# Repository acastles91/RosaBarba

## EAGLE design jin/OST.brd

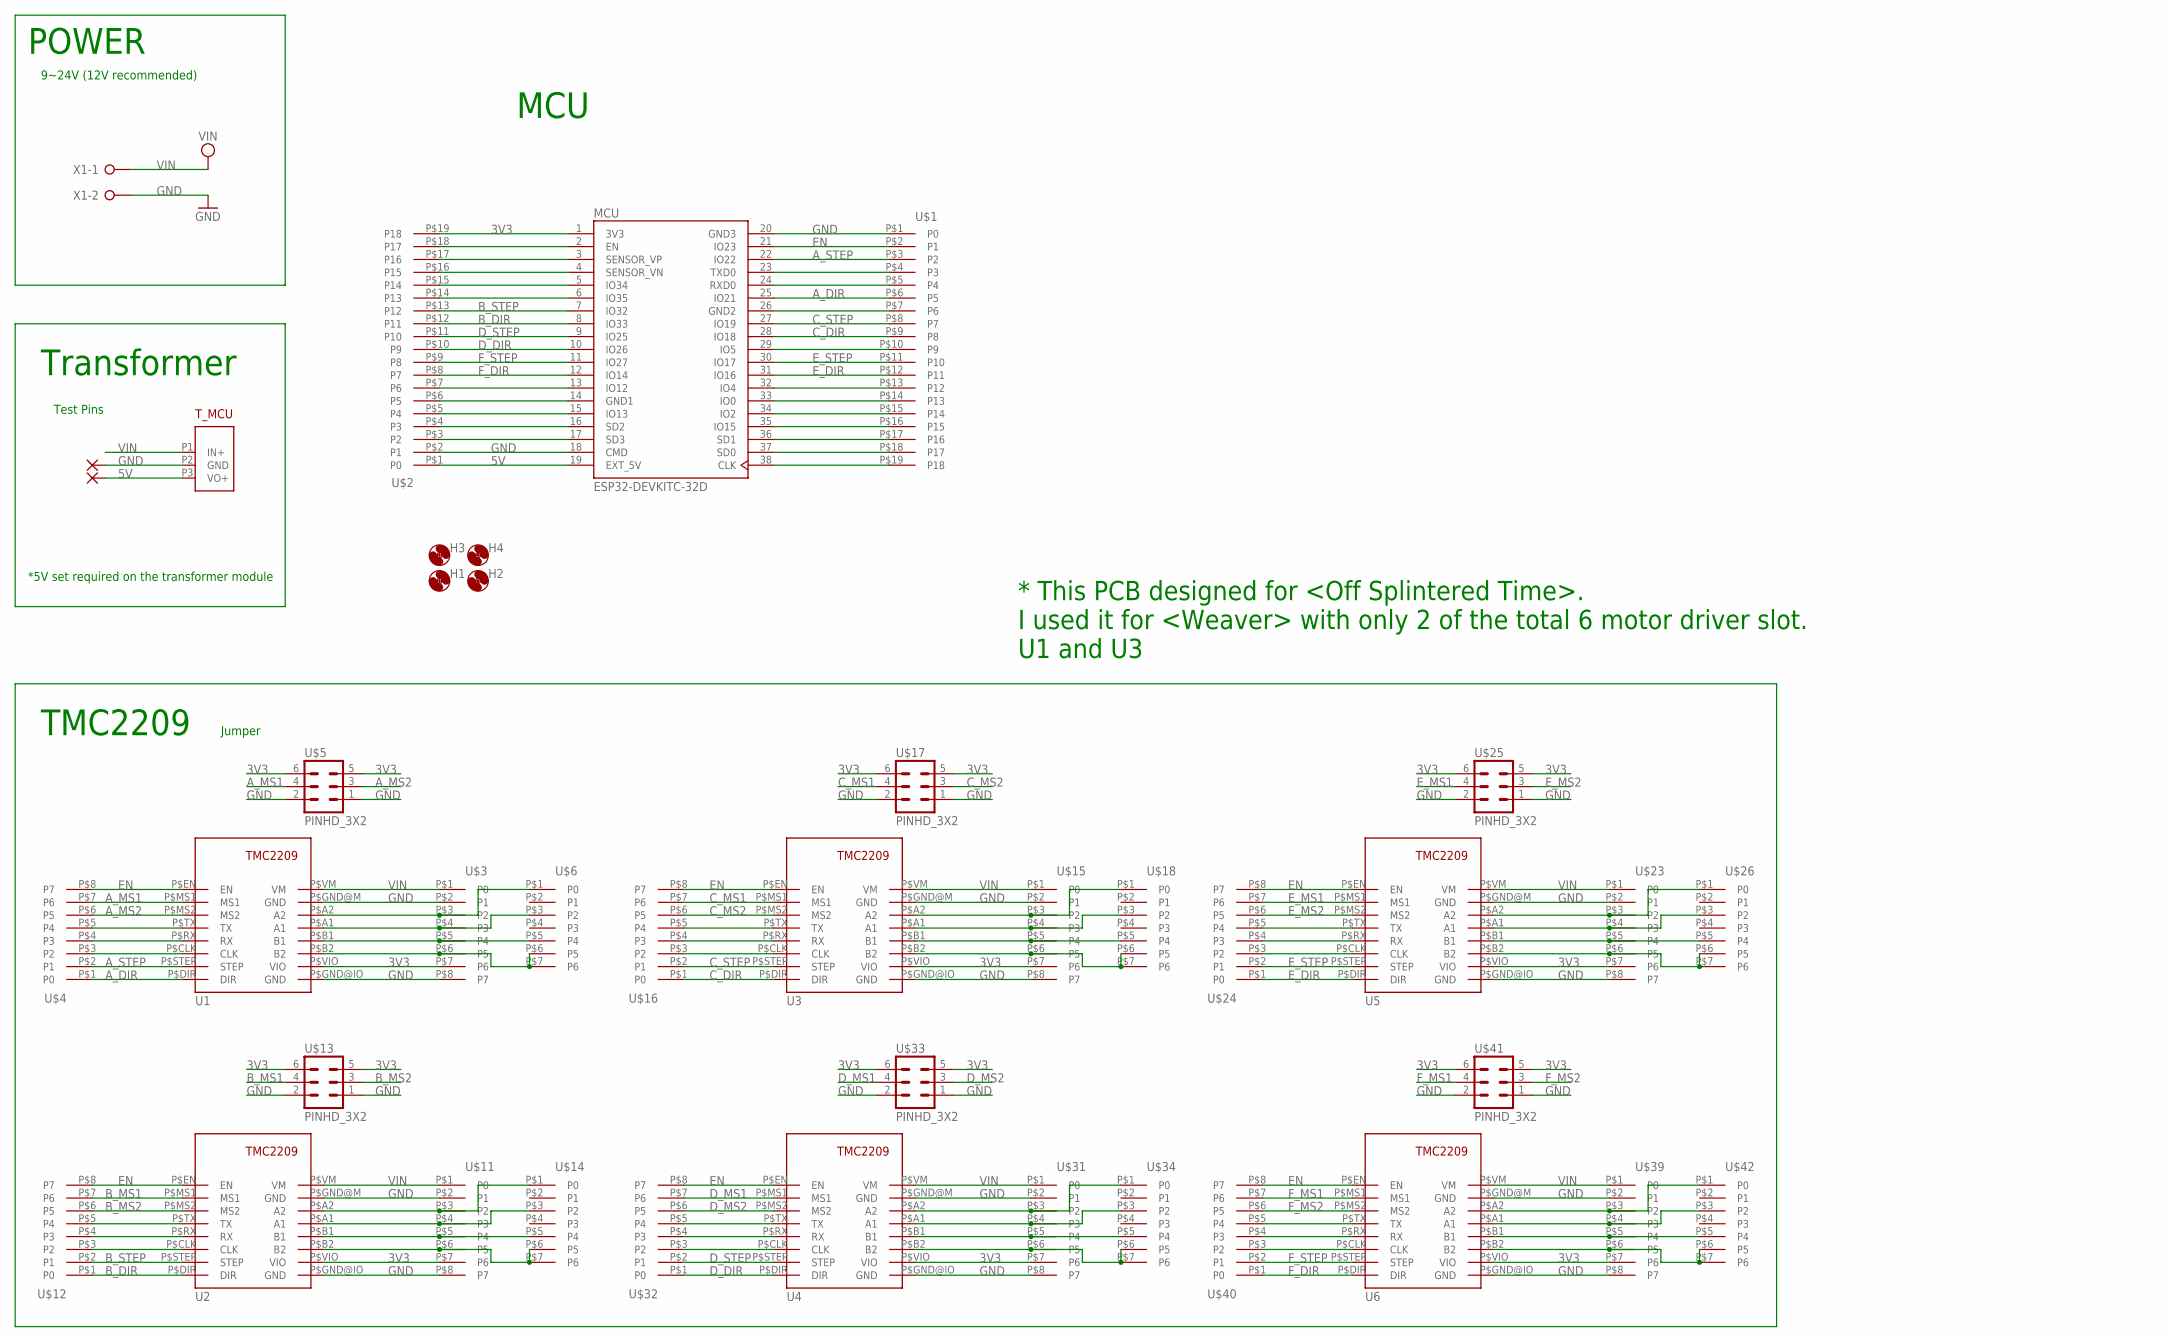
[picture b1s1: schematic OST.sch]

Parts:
H1, H2, H3, H4: MOUNT-HOLE3.2; 3,2
MCU: ESP32-DEVKITC-32D; MODULE_ESP32-DEVKITC-32D
PAD16, PAD17: 2,15/1,0
T_MCU: VOL_ADJ; FREEVOL
U1, U2, U3, U4, U5, U6: TMC2209_V3.1; TMC2209
U$1, U$2: PINHD_1X19; 19
U$3, U$4, U$11, U$12, U$15, U$16, U$23, U$24, U$31, U$32, U$39, U$40: PINHD_1X8; 8
U$5, U$13, U$17, U$25, U$33, U$41: PINHD_3X2; MA03-2
U$6, U$14, U$18, U$26, U$34, U$42: PINHD_1X7; 7
X1: W237-02P; W237-132

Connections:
3V3: MCU.1 (3V3), U1.P$VIO (VIO), U2.P$VIO (VIO), U3.P$VIO (VIO), U4.P$VIO (VIO), U5.P$VIO (VIO), U6.P$VIO (VIO), U$2.P$19 (P18), U$3.P$7 (P6), U$5.5, U$5.6, U$11.P$7 (P6), U$13.5, U$13.6, U$15.P$7 (P6), U$17.5, U$17.6, U$23.P$7 (P6), U$25.5, U$25.6, U$31.P$7 (P6), U$33.5, U$33.6, U$39.P$7 (P6), U$41.5, U$41.6
5V: MCU.19 (EXT_5V), PAD17.1, T_MCU.P3 (VO+), U$2.P$1 (P0)
A1: U1.P$A1 (A1), U$3.P$4 (P3), U$6.P$3 (P2)
A2: U1.P$A2 (A2), U$3.P$3 (P2), U$6.P$1 (P0)
A5: U2.P$A2 (A2), U$11.P$3 (P2), U$14.P$1 (P0)
A6: U2.P$A1 (A1), U$11.P$4 (P3), U$14.P$3 (P2)
A7: U3.P$A2 (A2), U$15.P$3 (P2), U$18.P$1 (P0)
A8: U3.P$A1 (A1), U$15.P$4 (P3), U$18.P$3 (P2)
A11: U5.P$A2 (A2), U$23.P$3 (P2), U$26.P$1 (P0)
A12: U5.P$A1 (A1), U$23.P$4 (P3), U$26.P$3 (P2)
A15: U4.P$A2 (A2), U$31.P$3 (P2), U$34.P$1 (P0)
A16: U4.P$A1 (A1), U$31.P$4 (P3), U$34.P$3 (P2)
A19: U6.P$A2 (A2), U$39.P$3 (P2), U$42.P$1 (P0)
A20: U6.P$A1 (A1), U$39.P$4 (P3), U$42.P$3 (P2)
A_DIR: MCU.25 (IO21), U1.P$DIR (DIR), U$1.P$6 (P5), U$4.P$1 (P0)
A_MS1: U1.P$MS1 (MS1), U$4.P$7 (P6), U$5.4
A_MS2: U1.P$MS2 (MS2), U$4.P$6 (P5), U$5.3
A_STEP: MCU.22 (IO22), U1.P$STEP (STEP), U$1.P$3 (P2), U$4.P$2 (P1)
B1: U1.P$B1 (B1), U$3.P$5 (P4), U$6.P$5 (P4)
B2: U1.P$B2 (B2), U$3.P$6 (P5), U$6.P$6 (P5), U$6.P$7 (P6)
B5: U2.P$B1 (B1), U$11.P$5 (P4), U$14.P$5 (P4)
B6: U2.P$B2 (B2), U$11.P$6 (P5), U$14.P$6 (P5), U$14.P$7 (P6)
B7: U3.P$B1 (B1), U$15.P$5 (P4), U$18.P$5 (P4)
B8: U3.P$B2 (B2), U$15.P$6 (P5), U$18.P$6 (P5), U$18.P$7 (P6)
B11: U5.P$B1 (B1), U$23.P$5 (P4), U$26.P$5 (P4)
B12: U5.P$B2 (B2), U$23.P$6 (P5), U$26.P$6 (P5), U$26.P$7 (P6)
B15: U4.P$B1 (B1), U$31.P$5 (P4), U$34.P$5 (P4)
B16: U4.P$B2 (B2), U$31.P$6 (P5), U$34.P$6 (P5), U$34.P$7 (P6)
B19: U6.P$B1 (B1), U$39.P$5 (P4), U$42.P$5 (P4)
B20: U6.P$B2 (B2), U$39.P$6 (P5), U$42.P$6 (P5), U$42.P$7 (P6)
B_DIR: MCU.8 (IO33), U2.P$DIR (DIR), U$2.P$12 (P11), U$12.P$1 (P0)
B_MS1: U2.P$MS1 (MS1), U$12.P$7 (P6), U$13.4
B_MS2: U2.P$MS2 (MS2), U$12.P$6 (P5), U$13.3
B_STEP: MCU.7 (IO32), U2.P$STEP (STEP), U$2.P$13 (P12), U$12.P$2 (P1)
C_DIR: MCU.28 (IO18), U3.P$DIR (DIR), U$1.P$9 (P8), U$16.P$1 (P0)
C_MS1: U3.P$MS1 (MS1), U$16.P$7 (P6), U$17.4
C_MS2: U3.P$MS2 (MS2), U$16.P$6 (P5), U$17.3
C_STEP: MCU.27 (IO19), U3.P$STEP (STEP), U$1.P$8 (P7), U$16.P$2 (P1)
D_DIR: MCU.10 (IO26), U4.P$DIR (DIR), U$2.P$10 (P9), U$32.P$1 (P0)
D_MS1: U4.P$MS1 (MS1), U$32.P$7 (P6), U$33.4
D_MS2: U4.P$MS2 (MS2), U$32.P$6 (P5), U$33.3
D_STEP: MCU.9 (IO25), U4.P$STEP (STEP), U$2.P$11 (P10), U$32.P$2 (P1)
EN: MCU.21 (IO23), U1.P$EN (EN), U2.P$EN (EN), U3.P$EN (EN), U4.P$EN (EN), U5.P$EN (EN), U6.P$EN (EN), U$1.P$2 (P1), U$4.P$8 (P7), U$12.P$8 (P7), U$16.P$8 (P7), U$24.P$8 (P7), U$32.P$8 (P7), U$40.P$8 (P7)
E_DIR: MCU.31 (IO16), U5.P$DIR (DIR), U$1.P$12 (P11), U$24.P$1 (P0)
E_MS1: U5.P$MS1 (MS1), U$24.P$7 (P6), U$25.4
E_MS2: U5.P$MS2 (MS2), U$24.P$6 (P5), U$25.3
E_STEP: MCU.30 (IO17), U5.P$STEP (STEP), U$1.P$11 (P10), U$24.P$2 (P1)
F_DIR: MCU.12 (IO14), U6.P$DIR (DIR), U$2.P$8 (P7), U$40.P$1 (P0)
F_MS1: U6.P$MS1 (MS1), U$40.P$7 (P6), U$41.4
F_MS2: U6.P$MS2 (MS2), U$40.P$6 (P5), U$41.3
F_STEP: MCU.11 (IO27), U6.P$STEP (STEP), U$2.P$9 (P8), U$40.P$2 (P1)
GND: MCU.18 (CMD), MCU.20 (GND3), PAD16.1, T_MCU.P2 (GND), U1.P$GND@IO (GND), U1.P$GND@M (GND), U2.P$GND@IO (GND), U2.P$GND@M (GND), U3.P$GND@IO (GND), U3.P$GND@M (GND), U4.P$GND@IO (GND), U4.P$GND@M (GND), U5.P$GND@IO (GND), U5.P$GND@M (GND), U6.P$GND@IO (GND), U6.P$GND@M (GND), U$1.P$1 (P0), U$2.P$2 (P1), U$3.P$2 (P1), U$3.P$8 (P7), U$5.1, U$5.2, U$11.P$2 (P1), U$11.P$8 (P7), U$13.1, U$13.2, U$15.P$2 (P1), U$15.P$8 (P7), U$17.1, U$17.2, U$23.P$2 (P1), U$23.P$8 (P7), U$25.1, U$25.2, U$31.P$2 (P1), U$31.P$8 (P7), U$33.1, U$33.2, U$39.P$2 (P1), U$39.P$8 (P7), U$41.1, U$41.2, X1.2
unnamed: U1.P$CLK (CLK), U$4.P$3 (P2)
unnamed: MCU.38 (CLK), U$1.P$19 (P18)
unnamed: U2.P$CLK (CLK), U$12.P$3 (P2)
unnamed: MCU.2 (EN), U$2.P$18 (P17)
unnamed: MCU.3 (SENSOR_VP), U$2.P$17 (P16)
unnamed: MCU.4 (SENSOR_VN), U$2.P$16 (P15)
unnamed: MCU.5 (IO34), U$2.P$15 (P14)
unnamed: MCU.6 (IO35), U$2.P$14 (P13)
unnamed: MCU.13 (IO12), U$2.P$7 (P6)
unnamed: MCU.14 (GND1), U$2.P$6 (P5)
unnamed: MCU.15 (IO13), U$2.P$5 (P4)
unnamed: MCU.16 (SD2), U$2.P$4 (P3)
unnamed: MCU.17 (SD3), U$2.P$3 (P2)
unnamed: U3.P$CLK (CLK), U$16.P$3 (P2)
unnamed: MCU.37 (SD0), U$1.P$18 (P17)
unnamed: MCU.36 (SD1), U$1.P$17 (P16)
unnamed: MCU.35 (IO15), U$1.P$16 (P15)
unnamed: MCU.34 (IO2), U$1.P$15 (P14)
unnamed: MCU.33 (IO0), U$1.P$14 (P13)
unnamed: MCU.32 (IO4), U$1.P$13 (P12)
unnamed: MCU.29 (IO5), U$1.P$10 (P9)
unnamed: MCU.26 (GND2), U$1.P$7 (P6)
unnamed: MCU.24 (RXD0), U$1.P$5 (P4)
unnamed: U5.P$CLK (CLK), U$24.P$3 (P2)
unnamed: U4.P$CLK (CLK), U$32.P$3 (P2)
unnamed: U6.P$CLK (CLK), U$40.P$3 (P2)
P$444: MCU.23 (TXD0), U$1.P$4 (P3)
RX: U1.P$RX (RX), U$4.P$4 (P3)
RX2: U2.P$RX (RX), U$12.P$4 (P3)
RX3: U3.P$RX (RX), U$16.P$4 (P3)
RX5: U5.P$RX (RX), U$24.P$4 (P3)
RX7: U4.P$RX (RX), U$32.P$4 (P3)
RX9: U6.P$RX (RX), U$40.P$4 (P3)
TX: U1.P$TX (TX), U$4.P$5 (P4)
TX2: U2.P$TX (TX), U$12.P$5 (P4)
TX3: U3.P$TX (TX), U$16.P$5 (P4)
TX5: U5.P$TX (TX), U$24.P$5 (P4)
TX7: U4.P$TX (TX), U$32.P$5 (P4)
TX9: U6.P$TX (TX), U$40.P$5 (P4)
VIN: T_MCU.P1 (IN+), U1.P$VM (VM), U2.P$VM (VM), U3.P$VM (VM), U4.P$VM (VM), U5.P$VM (VM), U6.P$VM (VM), U$3.P$1 (P0), U$11.P$1 (P0), U$15.P$1 (P0), U$23.P$1 (P0), U$31.P$1 (P0), U$39.P$1 (P0), X1.1

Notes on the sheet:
POWER
Transformer
MCU
Jumper
TMC2209
Test Pins
9~24V (12V recommended)
*5V set required on the transformer module
* This PCB designed for <Off Splintered Time>. I used it for <Weaver> with only 2 of the total 6 motor driver slot. U1 and U3

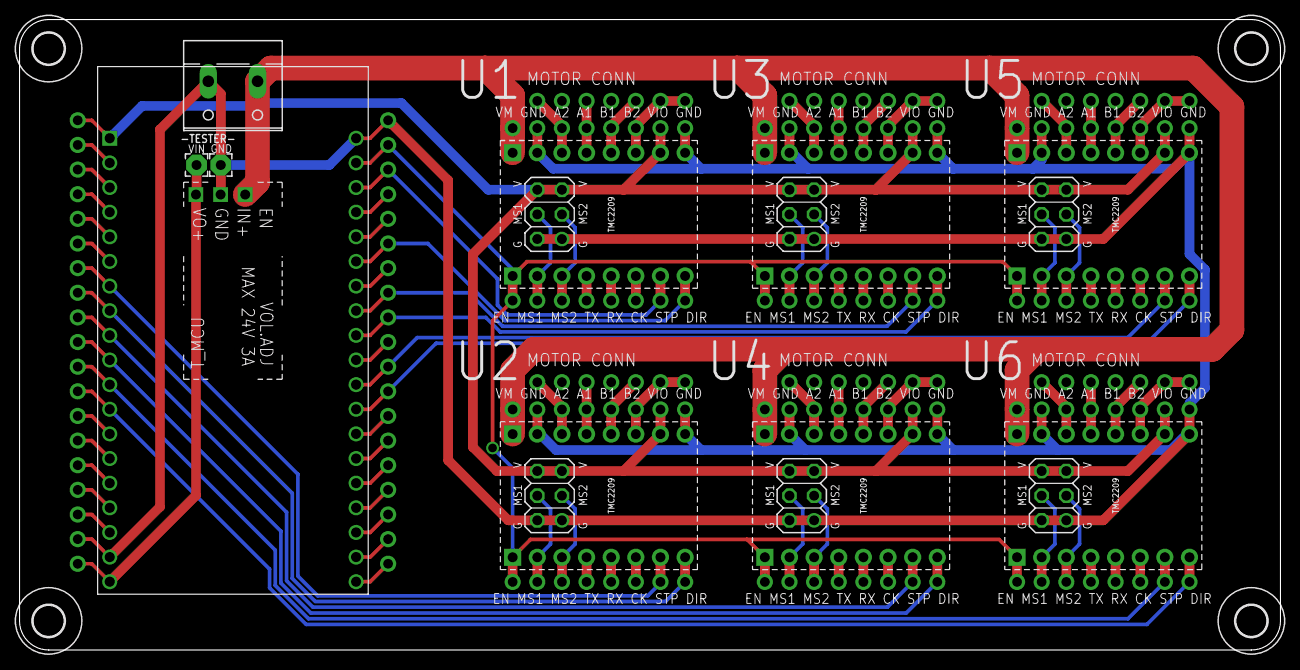
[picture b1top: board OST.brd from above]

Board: 2 copper layers, 130.0 x 65.0 mm, 41 parts (0 on the bottom side), 92 nets.

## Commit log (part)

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2022-07-28 Working with duration
2022-12-15 last working
2022-12-15 Second frame, speeds and direction approved by Nils
2023-04-28 Only one motor, not using AccelStepper, much cleaner step wave
2023-06-15 Agnieska Polska before moving back to Rosa
2023-06-15 modified, added second motor
2023-07-12 Two motors, no libraries, for Rosa Barba
2023-07-12 Speeds approved by Nils
2026-06-18 fixed startup
2026-06-18 added phonetic-script
2026-06-18 added Spiral
2026-06-18 added Spiral 2
2026-06-18 fixed normal install script
